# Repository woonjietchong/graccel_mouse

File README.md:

# graccel_mouse
Mouse hardware and software design based on accelerometer

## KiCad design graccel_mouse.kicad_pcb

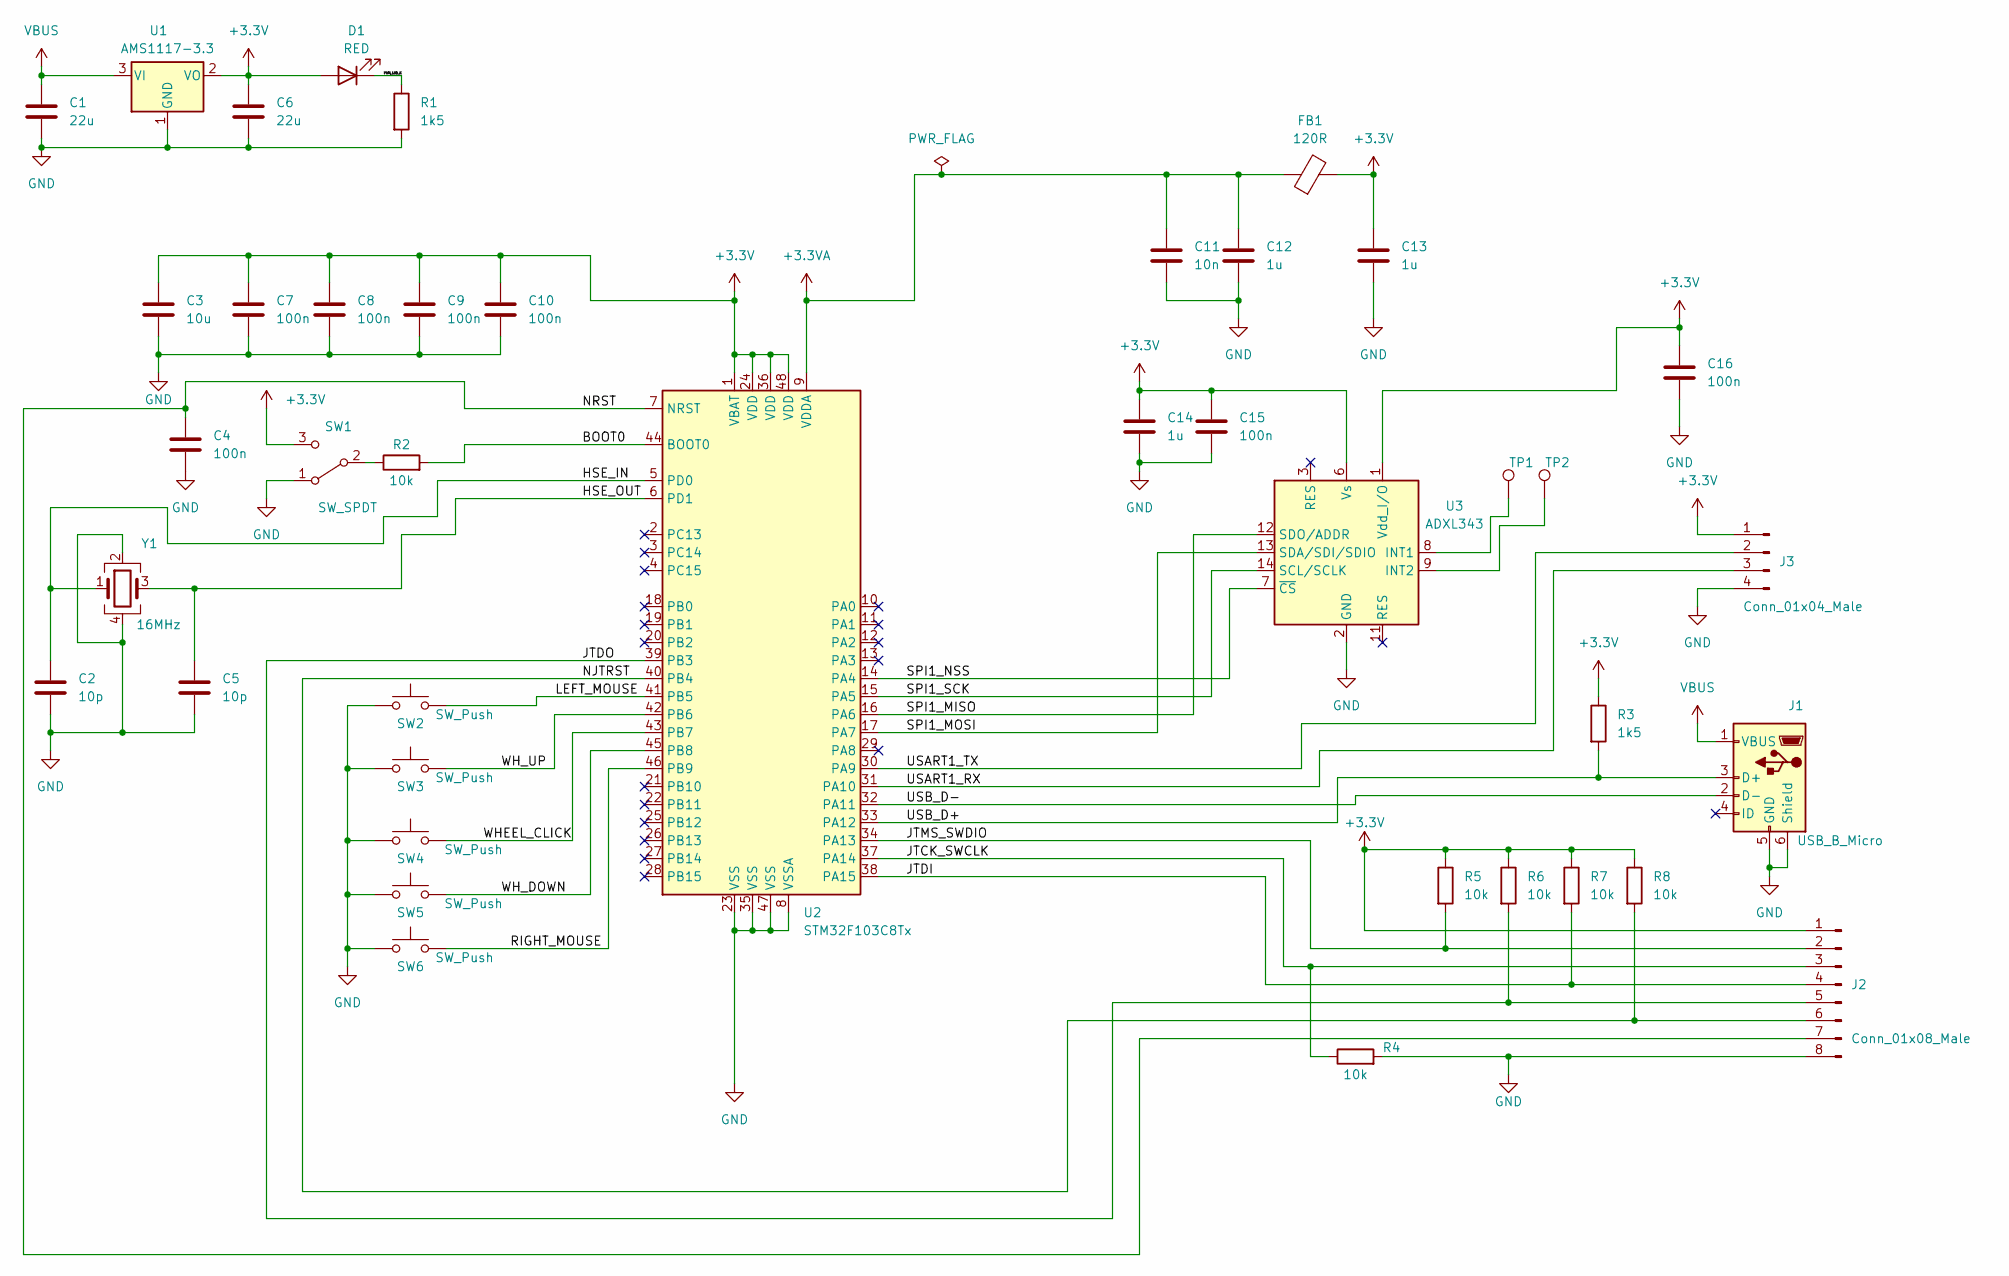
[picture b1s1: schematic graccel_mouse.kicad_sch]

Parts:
C1, C6: 22u; C_0805_2012Metric
C2, C5: 10p; C_0402_1005Metric
C3: 10u; C_0603_1608Metric
C4, C7, C8, C9, C10, C15, C16: 100n; C_0402_1005Metric
C11: 10n; C_0402_1005Metric
C12, C13, C14: 1u; C_0402_1005Metric
D1: RED; LED_0603_1608Metric
FB1: 120R; L_0603_1608Metric
J1: USB_B_Micro; USB_Micro-B_Molex_47346-0001
J2: Conn_01x08_Male; PinHeader_1x08_P2.54mm_Vertical
J3: Conn_01x04_Male; PinHeader_1x04_P2.54mm_Vertical
R1, R3: 1k5; R_0402_1005Metric
R2, R4, R5, R6, R7, R8: 10k; R_0402_1005Metric
SW1: SW_SPDT; SW_SPDT_PCM12
SW2, SW3, SW4, SW5, SW6: SW_Push; SW_PUSH_6mm
TP1, TP2: TestPoint; TestPoint_Pad_D1.0mm
U1: AMS1117-3.3; SOT-223-3_TabPin2
U2: STM32F103C8Tx; LQFP-48_7x7mm_P0.5mm
U3: ADXL343; LGA-14_3x5mm_P0.8mm_LayoutBorder1x6y
Y1: 16MHz; Crystal_SMD_3225-4Pin_3.2x2.5mm

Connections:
+3.3V: C3.1, C6.1, C7.1, C8.1, C9.1, C10.1, C13.1, C14.1, C15.1, C16.1, D1.2 (A), FB1.2, J2.1, J3.1, R3.1, R5.1, R6.1, R7.1, R8.1, SW1.3 (C), U1.2 (VO), U2.1 (VBAT), U2.24 (VDD), U2.36 (VDD), U2.48 (VDD), U3.1 (Vdd_I/O), U3.6 (Vs)
+3.3VA: C11.1, C12.1, FB1.1, U2.9 (VDDA)
/BOOT0: R2.2, U2.44 (BOOT0)
/HSE_IN: C2.1, U2.5 (PD0), Y1.1
/HSE_OUT: C5.1, U2.6 (PD1), Y1.3
/JTCK_SWCLK: J2.3, R4.1, U2.37 (PA14)
/JTDI: J2.4, R7.2, U2.38 (PA15)
/JTDO: J2.5, R6.2, U2.39 (PB3)
/JTMS_SWDIO: J2.2, R5.2, U2.34 (PA13)
/LEFT_MOUSE: SW2.2, U2.41 (PB5)
/NJTRST: J2.6, R8.2, U2.40 (PB4)
/NRST: C4.1, J2.7, U2.7 (NRST)
/PWR_LED_K: D1.1 (K), R1.1
/RIGHT_MOUSE: SW6.2, U2.46 (PB9)
/SPI1_MISO: U2.16 (PA6), U3.12 (SDO/ADDR)
/SPI1_MOSI: U2.17 (PA7), U3.13 (SDA/SDI/SDIO)
/SPI1_NSS: U2.14 (PA4), U3.7 (~CS)
/SPI1_SCK: U2.15 (PA5), U3.14 (SCL/SCLK)
/USART1_RX: J3.3, U2.31 (PA10)
/USART1_TX: J3.2, U2.30 (PA9)
/USB_D+: J1.3 (D+), R3.2, U2.33 (PA12)
/USB_D-: J1.2 (D-), U2.32 (PA11)
/WHEEL_CLICK: SW4.2, U2.43 (PB7)
/WH_DOWN: SW5.2, U2.45 (PB8)
/WH_UP: SW3.2, U2.42 (PB6)
GND: C1.2, C2.2, C3.2, C4.2, C5.2, C6.2, C7.2, C8.2, C9.2, C10.2, C11.2, C12.2, C13.2, C14.2, C15.2, C16.2, J1.5 (GND), J1.6 (Shield), J2.8, J3.4, R1.2, R4.2, SW1.1 (A), SW2.1, SW3.1, SW4.1, SW5.1, SW6.1, U1.1 (GND), U2.8 (VSSA), U2.23 (VSS), U2.35 (VSS), U2.47 (VSS), U3.2 (GND), U3.4 (GND), U3.5 (GND), Y1.2, Y1.4
unnamed: R2.1, SW1.2 (B)
unnamed: TP1.1, U3.8 (INT1)
unnamed: TP2.1, U3.9 (INT2)
VBUS: C1.1, J1.1 (VBUS), U1.3 (VI)

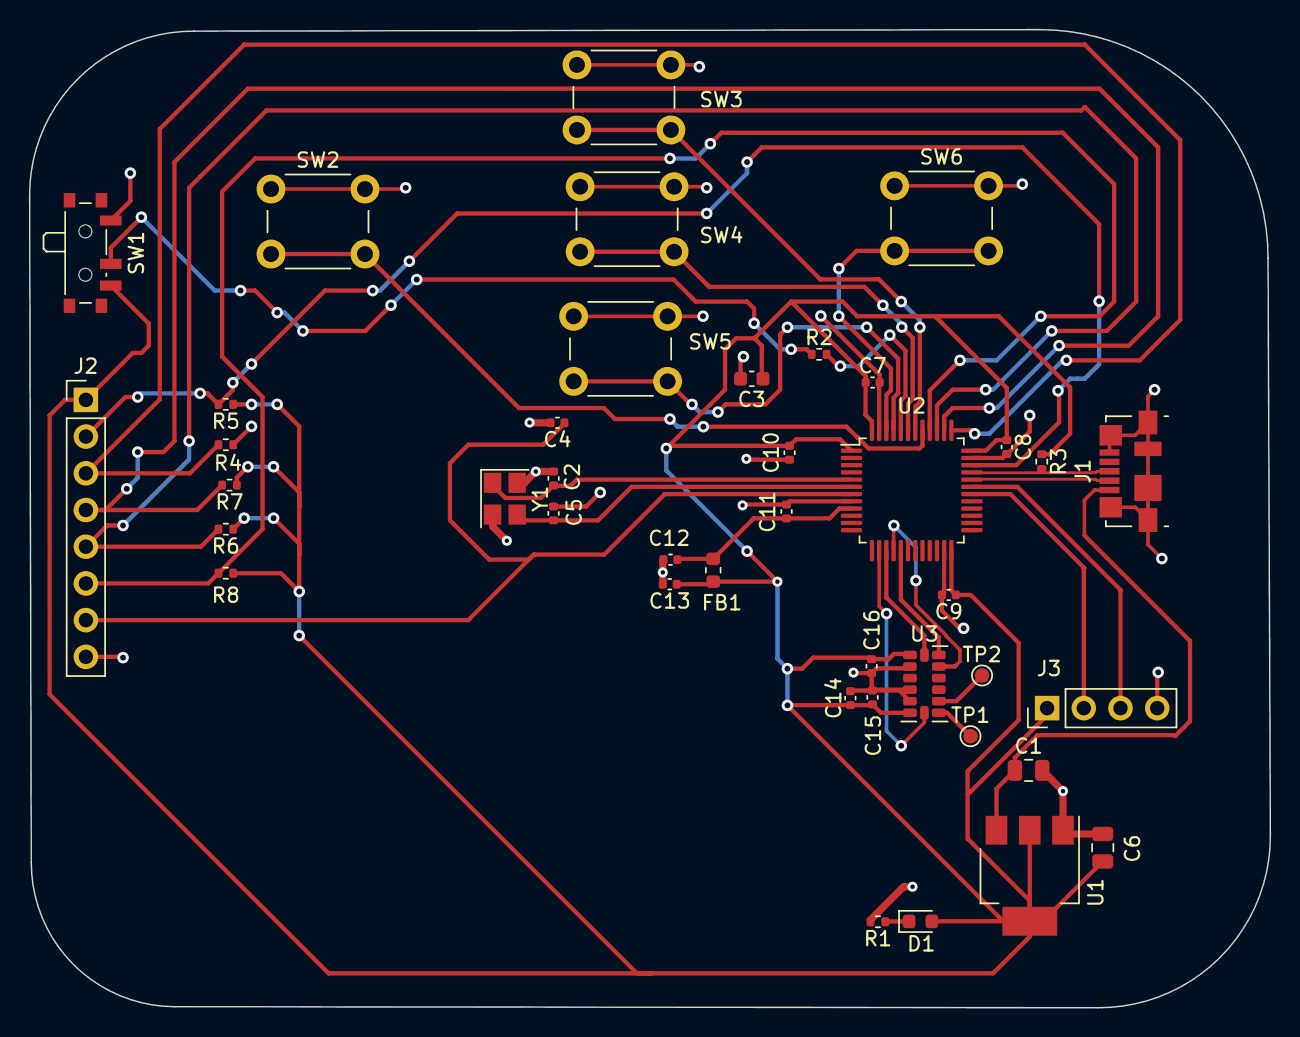
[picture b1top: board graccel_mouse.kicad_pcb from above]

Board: 2 copper layers, 85.9 x 67.7 mm, 41 parts (0 on the bottom side), 30 nets.

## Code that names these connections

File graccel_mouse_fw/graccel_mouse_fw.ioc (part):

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Mcu.Name=STM32F103C(8-B)Tx
Mcu.Package=LQFP48
Mcu.UserName=STM32F103C8Tx
PA11.Mode=Device
PA11.Signal=USB_DM
PA12.Mode=Device
PA12.Signal=USB_DP
PA13.Mode=Serial_Wire
PA13.Signal=SYS_JTMS-SWDIO
PA14.Mode=Serial_Wire
PA14.Signal=SYS_JTCK-SWCLK
PD0-OSC_IN.Mode=HSE-External-Oscillator
PD0-OSC_IN.Signal=RCC_OSC_IN
PD1-OSC_OUT.Mode=HSE-External-Oscillator
PD1-OSC_OUT.Signal=RCC_OSC_OUT
RCC.HSEDivPLL=RCC_HSE_PREDIV_DIV2
RCC.HSE_VALUE=16000000
RCC.SYSCLKFreq_VALUE=72000000
RCC.SYSCLKSource=RCC_SYSCLKSOURCE_PLLCLK
board=custom

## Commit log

2022-07-20 init with decoupling capacitor and accelerometer
2022-07-21 complete mouse with button
2022-07-21 complete pcb design and add gerber, bom and cpl
2022-08-06 Initial firmware with Clock and USB
2022-08-06 add usb device and swd
